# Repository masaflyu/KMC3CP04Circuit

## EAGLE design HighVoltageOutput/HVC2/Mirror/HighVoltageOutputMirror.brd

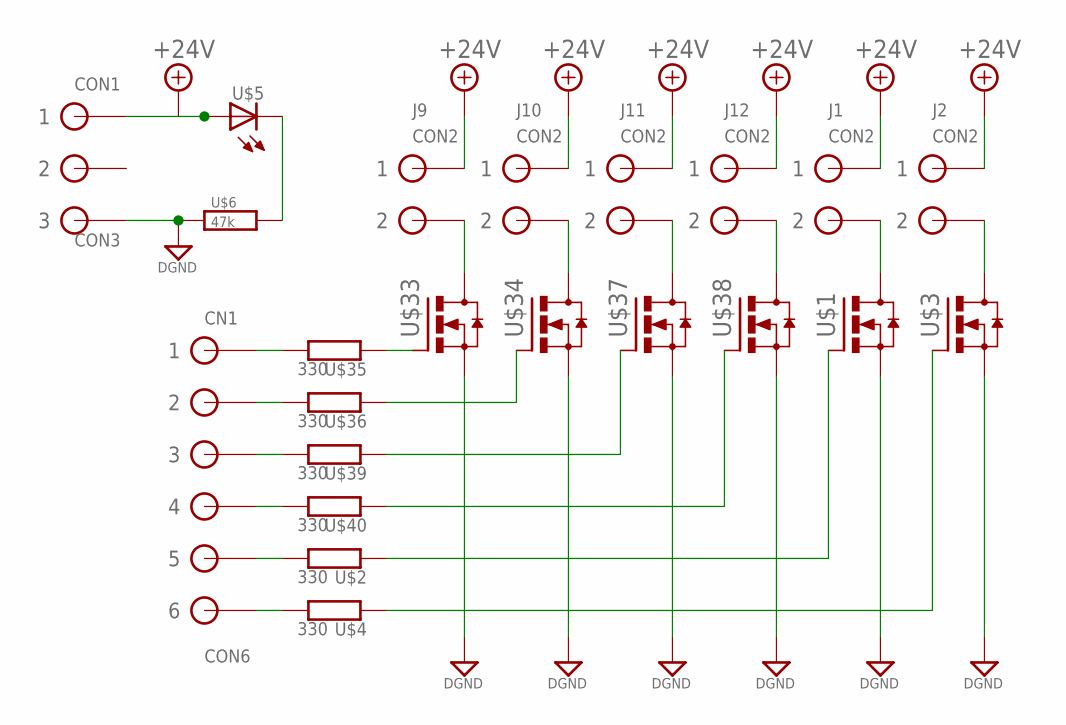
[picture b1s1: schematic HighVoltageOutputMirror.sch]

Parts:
CN1: CON6
CON1: CON3
J1, J2, J9, J10, J11, J12: CON2
U$1, U$3, U$33, U$34, U$37, U$38: TO-252(MOS-FET_N)TO-252FORHAND; TO-252FORHAND
U$2, U$4, U$35, U$36, U$39, U$40: 330; 1/4W-H4_(0207/10)
U$5: LED(砲弾型)3; LED3MM
U$6: 47k; 0805(JIS2012)HAND

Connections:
+24V: CON1.P$1 (1), J1.P$1 (1), J2.P$1 (1), J9.P$1 (1), J10.P$1 (1), J11.P$1 (1), J12.P$1 (1), U$5.A
DGND: CON1.P$3 (3), U$1.2 (S), U$3.2 (S), U$6.1, U$33.2 (S), U$34.2 (S), U$37.2 (S), U$38.2 (S)
unnamed: CN1.P$5 (5), U$2.2
unnamed: U$1.1 (G), U$2.1
unnamed: J1.P$2 (2), U$1.3 (D)
unnamed: CN1.P$6 (6), U$4.2
unnamed: U$3.1 (G), U$4.1
unnamed: J2.P$2 (2), U$3.3 (D)
unnamed: CN1.P$2 (2), U$36.2
unnamed: U$5.K, U$6.2
unnamed: CN1.P$1 (1), U$35.2
unnamed: CN1.P$3 (3), U$39.2
unnamed: CN1.P$4 (4), U$40.2
unnamed: U$33.1 (G), U$35.1
unnamed: U$34.1 (G), U$36.1
unnamed: J9.P$2 (2), U$33.3 (D)
unnamed: J10.P$2 (2), U$34.3 (D)
unnamed: U$37.1 (G), U$39.1
unnamed: U$38.1 (G), U$40.1
unnamed: J11.P$2 (2), U$37.3 (D)
unnamed: J12.P$2 (2), U$38.3 (D)

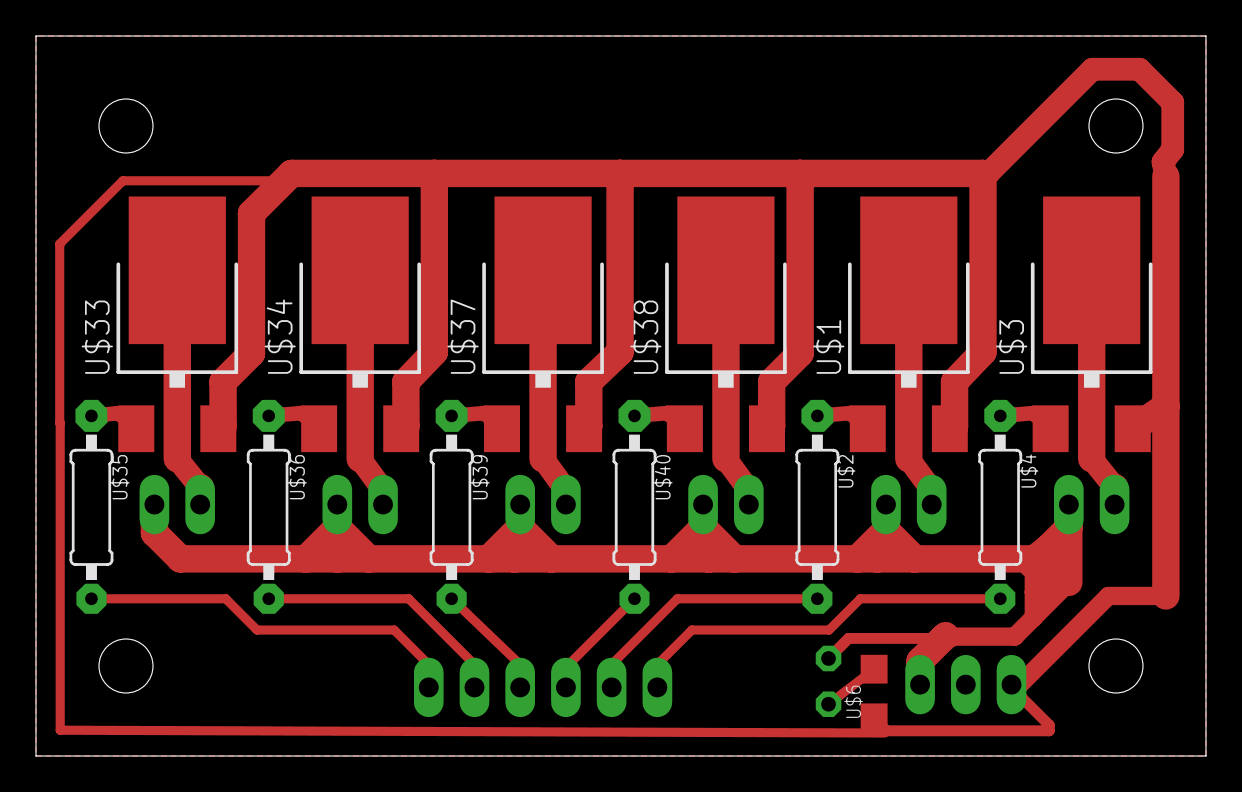
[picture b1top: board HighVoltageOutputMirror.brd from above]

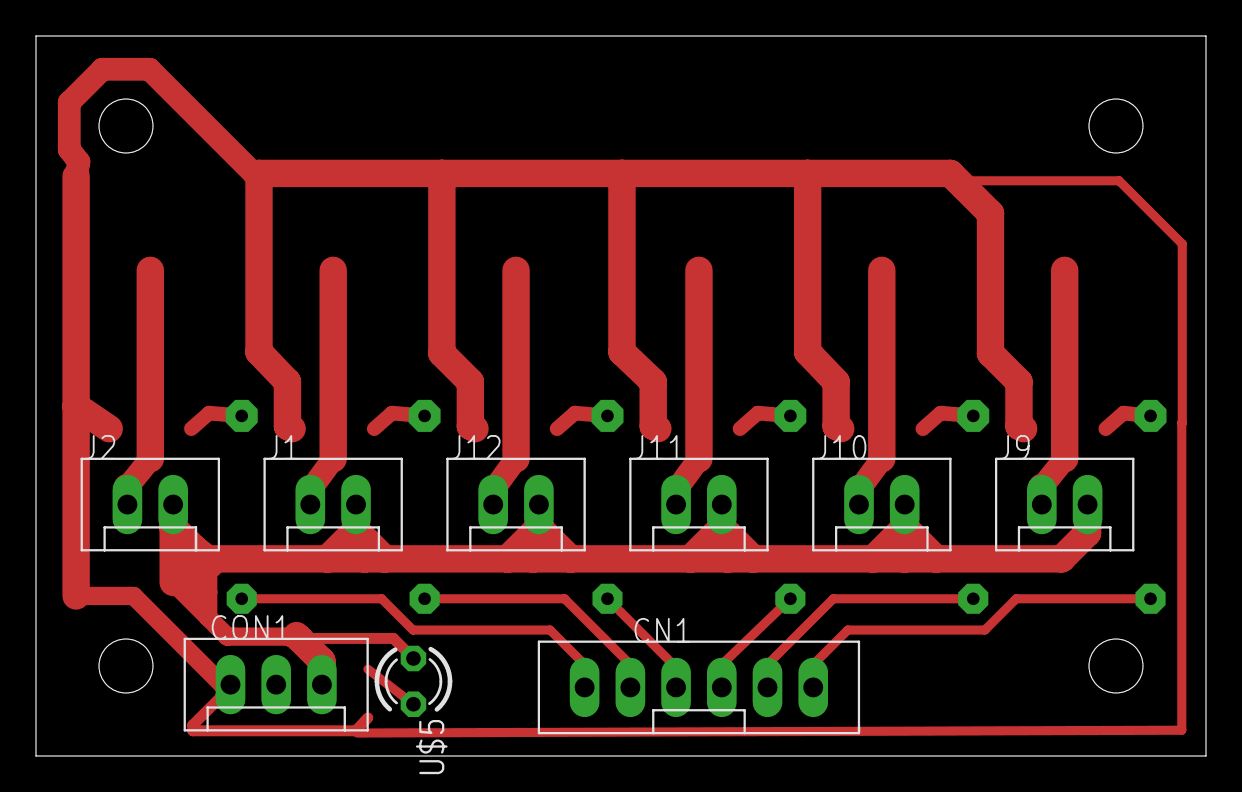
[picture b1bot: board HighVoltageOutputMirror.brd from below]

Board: 2 copper layers, 65.0 x 40.0 mm, 22 parts (9 on the bottom side), 21 nets.

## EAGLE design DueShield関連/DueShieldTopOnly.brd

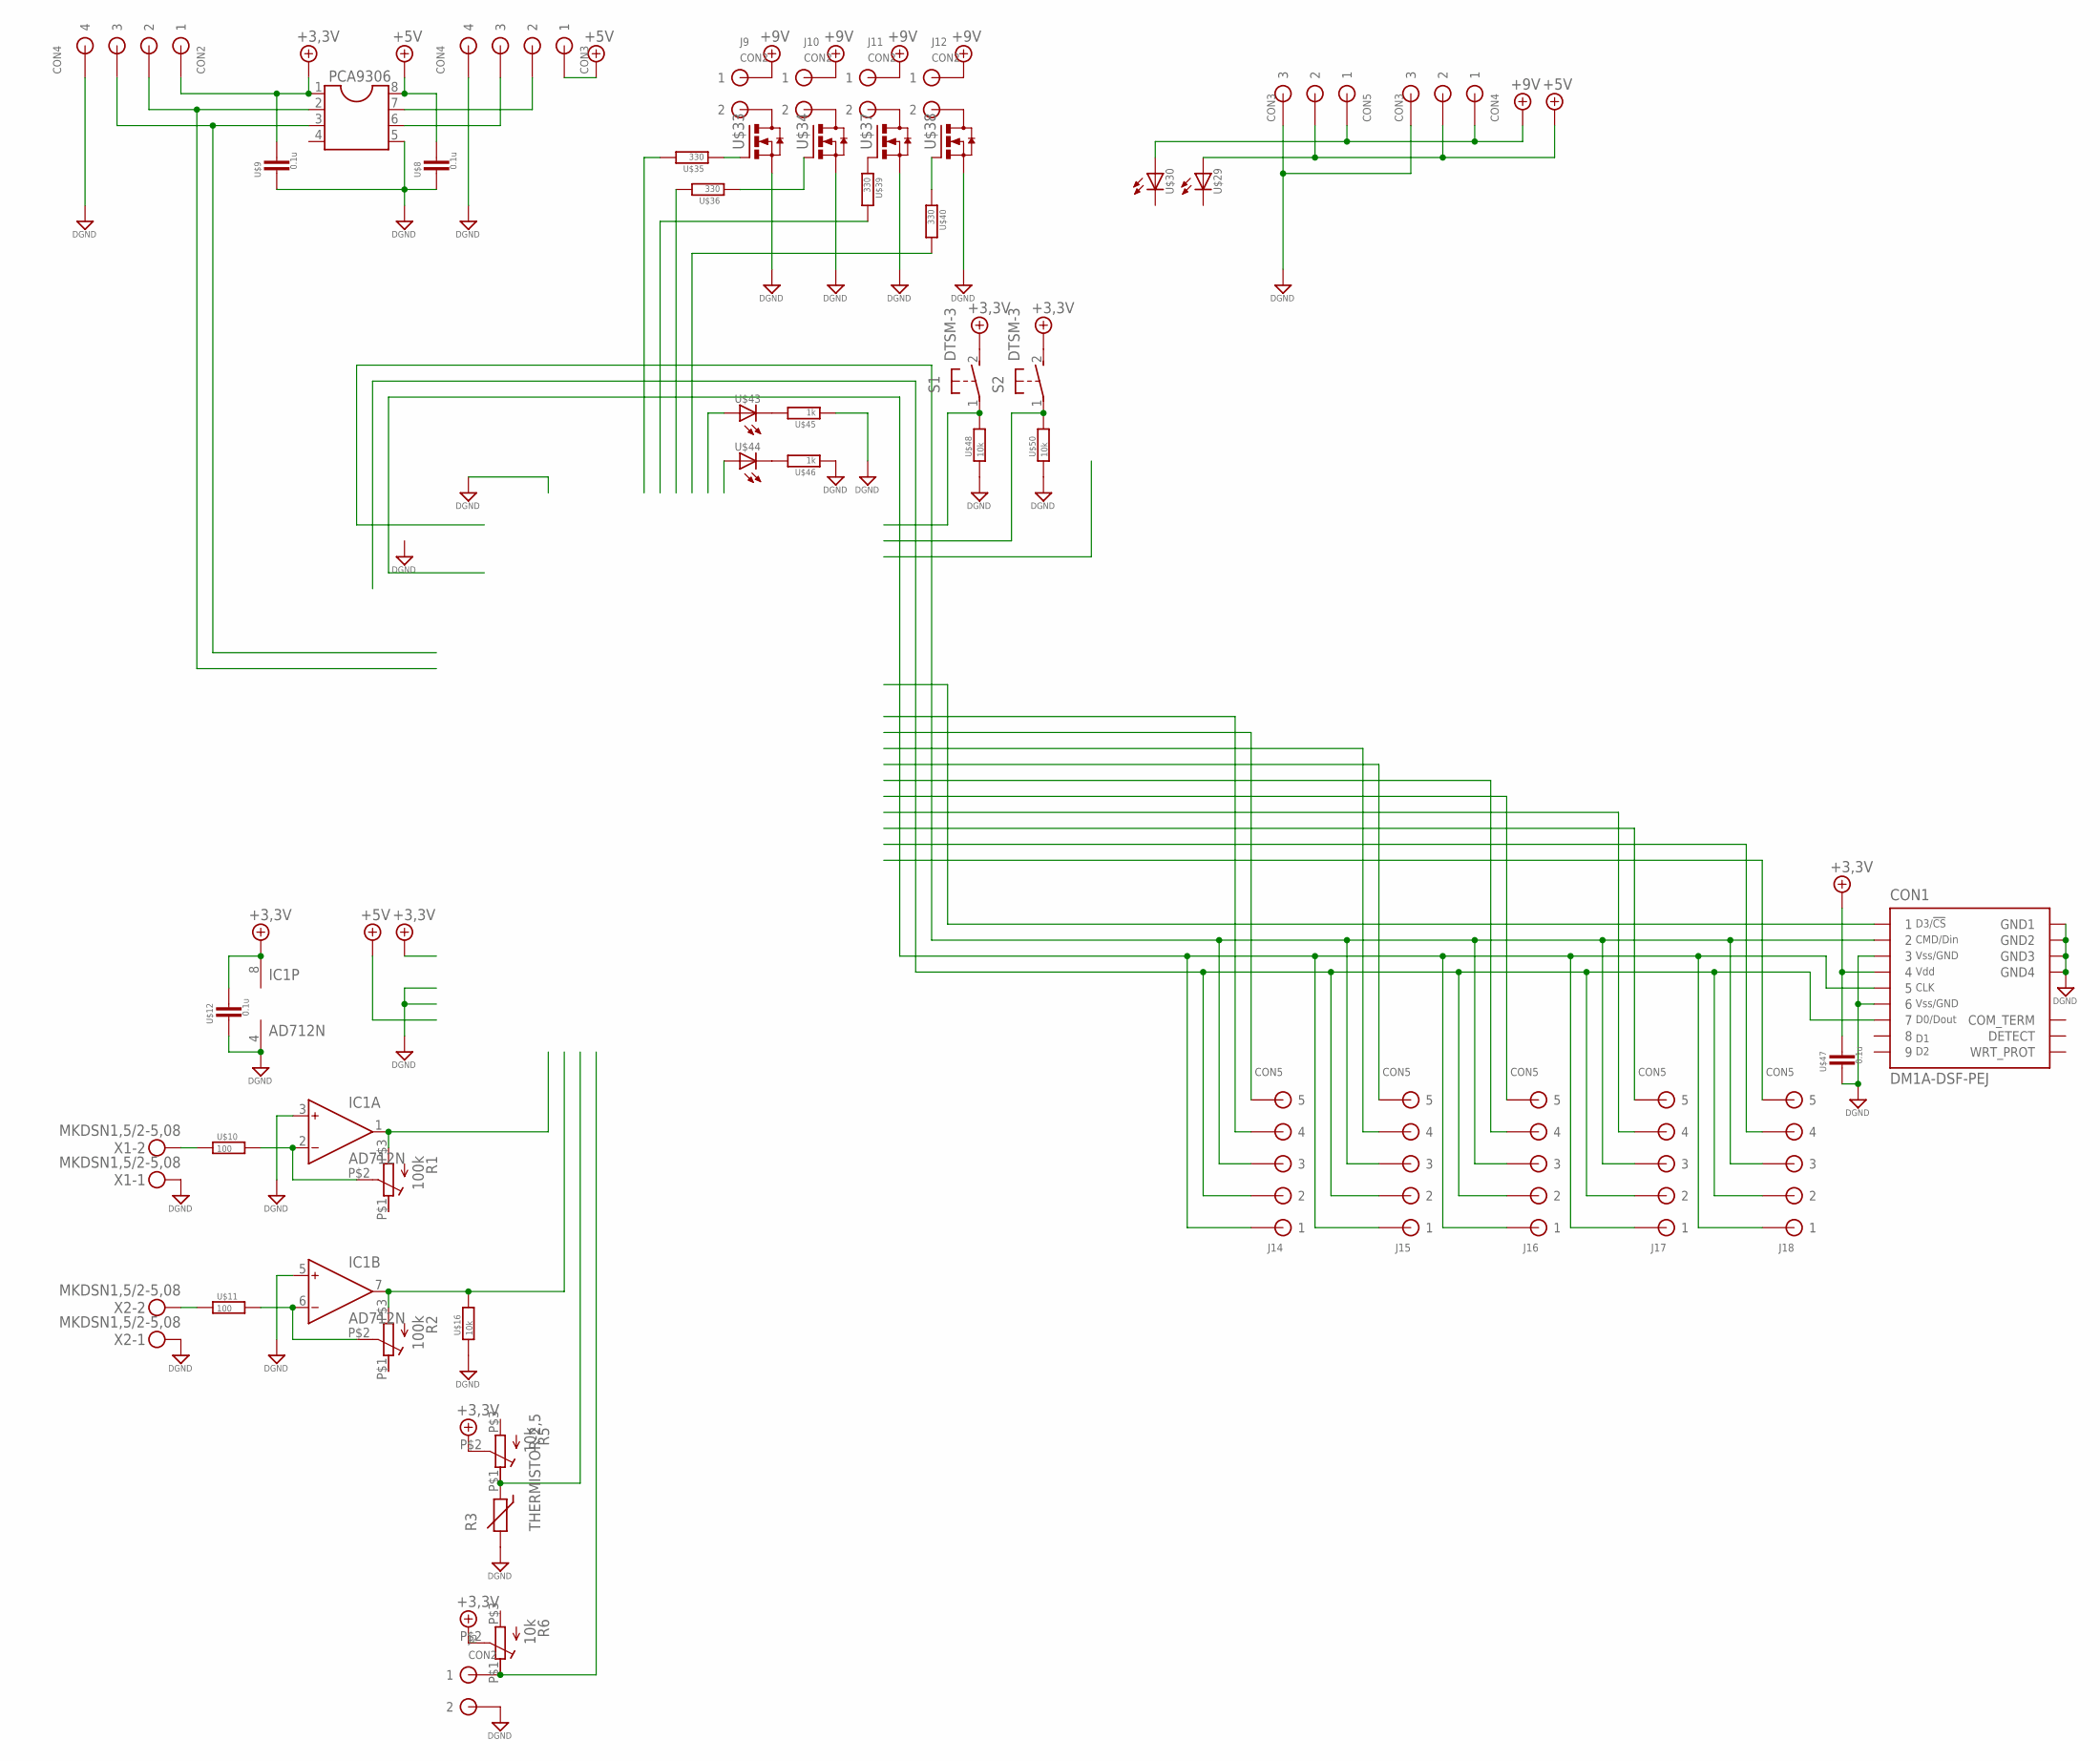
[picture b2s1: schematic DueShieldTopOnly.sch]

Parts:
CON1: DM1A-DSF-PEJ
CON2, CON3: CON4
CON4, CON5: CON3
IC1: AD712N; DIL08
J2, J9, J10, J11, J12: CON2
J14, J15, J16, J17, J18: CON5
PCA9306: DIL8; DIL08
R1, R2: 100k; GF063PB
R3: THERMISTOR-2,5; RS-2,5
R5, R6: 10k; GF063PB
S1, S2: DTSM-3
U$8, U$9, U$12, U$47: 0.1u; 0805
U$10, U$11: 100; 0805
U$16, U$48, U$50: 10k; 0805
U$29, U$30, U$43, U$44: LED(砲弾型)3; LED3MM
U$33, U$34, U$37, U$38: TO-252(MOS-FET_N); TO-252
U$35, U$36, U$39, U$40: 330; 0805
U$45, U$46: 1k; 0805
X1, X2: MKDSN1,5/2-5,08

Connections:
+3.3V: CON1.4, CON2.P$1 (1), IC1.8 (V+), PCA9306.1, R5.P$2 (S), R6.P$2 (S), S1.2, S2.2, U$9.1, U$12.1, U$47.1
+5V: CON3.P$1 (1), CON4.P$2 (2), CON5.P$2 (2), PCA9306.8, U$8.1, U$29.A
+5V1: U$43.A
+9V: CON4.P$1 (1), CON5.P$1 (1), J9.P$1 (1), J10.P$1 (1), J11.P$1 (1), J12.P$1 (1), U$30.A
+9V1: U$44.A
DGND: CON1.3, CON1.6, CON1.GND1, CON1.GND2, CON1.GND3, CON1.GND4, CON2.P$4 (4), CON3.P$4 (4), CON4.P$3 (3), CON5.P$3 (3), IC1.3 (IN+), IC1.4 (V-), IC1.5 (IN+), J2.P$2 (2), PCA9306.5, R3.2, U$8.2, U$9.2, U$12.2, U$16.1, U$33.2 (S), U$34.2 (S), U$37.2 (S), U$38.2 (S), U$45.1, U$46.1, U$47.2, U$48.1, U$50.1, X1.1, X2.1
unnamed: CON1.7, J14.P$2 (2), J15.P$2 (2), J16.P$2 (2), J17.P$2 (2), J18.P$2 (2)
unnamed: S1.1, U$48.2
unnamed: CON2.P$2 (2), PCA9306.2
unnamed: CON1.5, J14.P$1 (1), J15.P$1 (1), J16.P$1 (1), J17.P$1 (1), J18.P$1 (1)
unnamed: CON2.P$3 (3), PCA9306.3
unnamed: CON3.P$2 (2), PCA9306.7
unnamed: CON3.P$3 (3), PCA9306.6
unnamed: IC1.2 (IN-), R1.P$2 (S), U$10.2
unnamed: IC1.6 (IN-), R2.P$2 (S), U$11.2
unnamed: U$11.1, X2.2
unnamed: U$10.1, X1.2
unnamed: J2.P$1 (1), R6.P$1 (E)
unnamed: IC1.1 (OUT), R1.P$3 (A)
unnamed: IC1.7 (OUT), R2.P$3 (A), U$16.2
unnamed: R3.1, R5.P$1 (E)
unnamed: U$43.K, U$45.2
unnamed: U$33.1 (G), U$35.1
unnamed: U$34.1 (G), U$36.1
unnamed: J9.P$2 (2), U$33.3 (D)
unnamed: J10.P$2 (2), U$34.3 (D)
unnamed: U$37.1 (G), U$39.1
unnamed: U$38.1 (G), U$40.1
unnamed: J11.P$2 (2), U$37.3 (D)
unnamed: J12.P$2 (2), U$38.3 (D)
unnamed: U$44.K, U$46.2
unnamed: CON1.2, J14.P$3 (3), J15.P$3 (3), J16.P$3 (3), J17.P$3 (3), J18.P$3 (3)
unnamed: S2.1, U$50.2

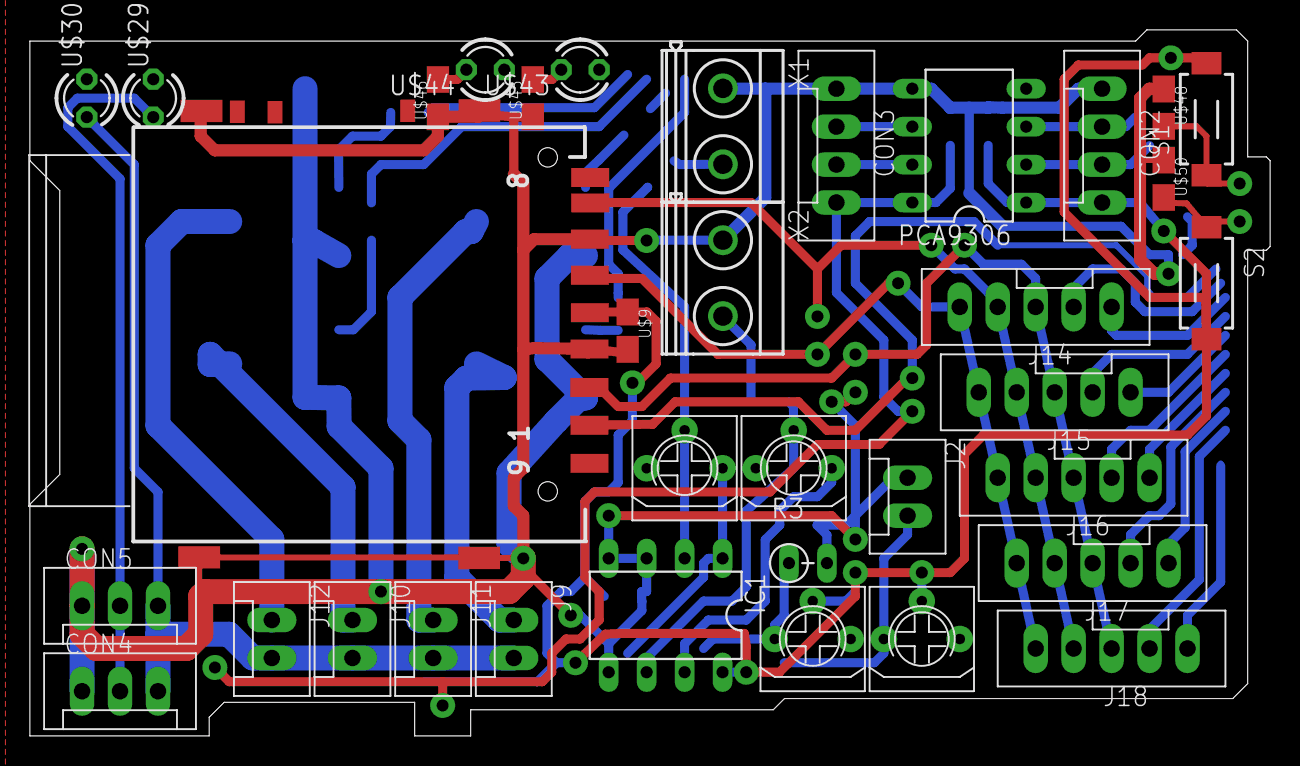
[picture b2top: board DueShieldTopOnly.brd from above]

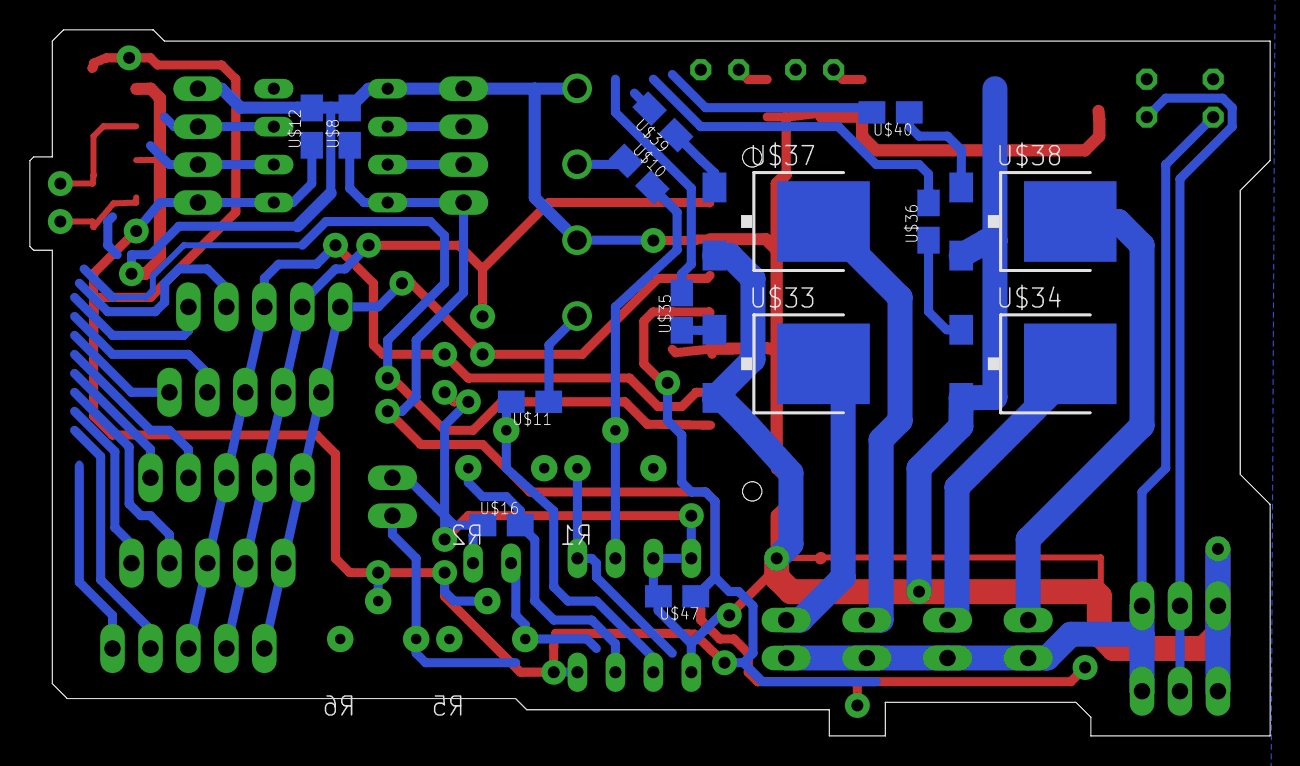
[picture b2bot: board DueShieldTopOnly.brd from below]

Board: 2 copper layers, 83.0 x 47.2 mm, 49 parts (14 on the bottom side), 31 nets.

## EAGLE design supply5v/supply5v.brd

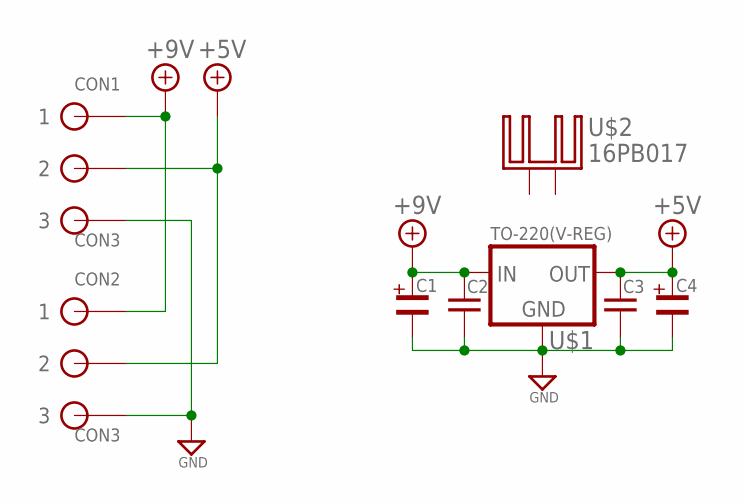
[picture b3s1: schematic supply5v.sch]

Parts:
C1, C4: コンデンサ(電解)E2.5-5; D=1,φ=5
C2, C3: (コンデンサ)セラミック050-024X044; C050-024X044
CON1, CON2: CON3
U$1: TO-220(V-REG); TO-220
U$2: 16PB017

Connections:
+5V: C3.1, C4.+, CON1.P$2 (2), CON2.P$2 (2), U$1.3 (OUT)
+9V: C1.+, C2.1, CON1.P$1 (1), CON2.P$1 (1), U$1.2 (IN)
GND: C1.-, C2.2, C3.2, C4.-, CON1.P$3 (3), CON2.P$3 (3), U$1.1 (GND)

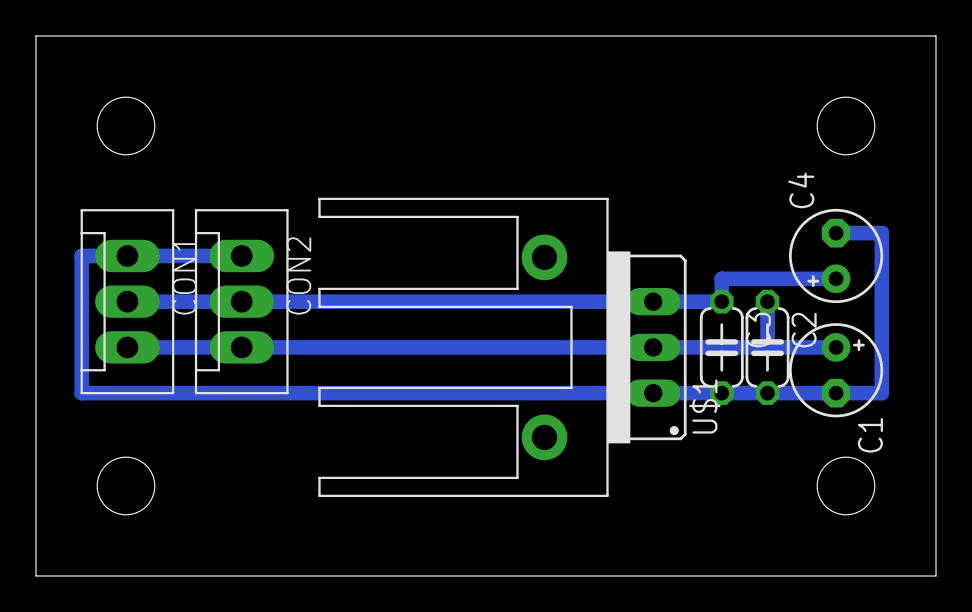
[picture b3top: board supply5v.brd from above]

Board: 2 copper layers, 50.0 x 30.0 mm, 8 parts (0 on the bottom side), 3 nets.

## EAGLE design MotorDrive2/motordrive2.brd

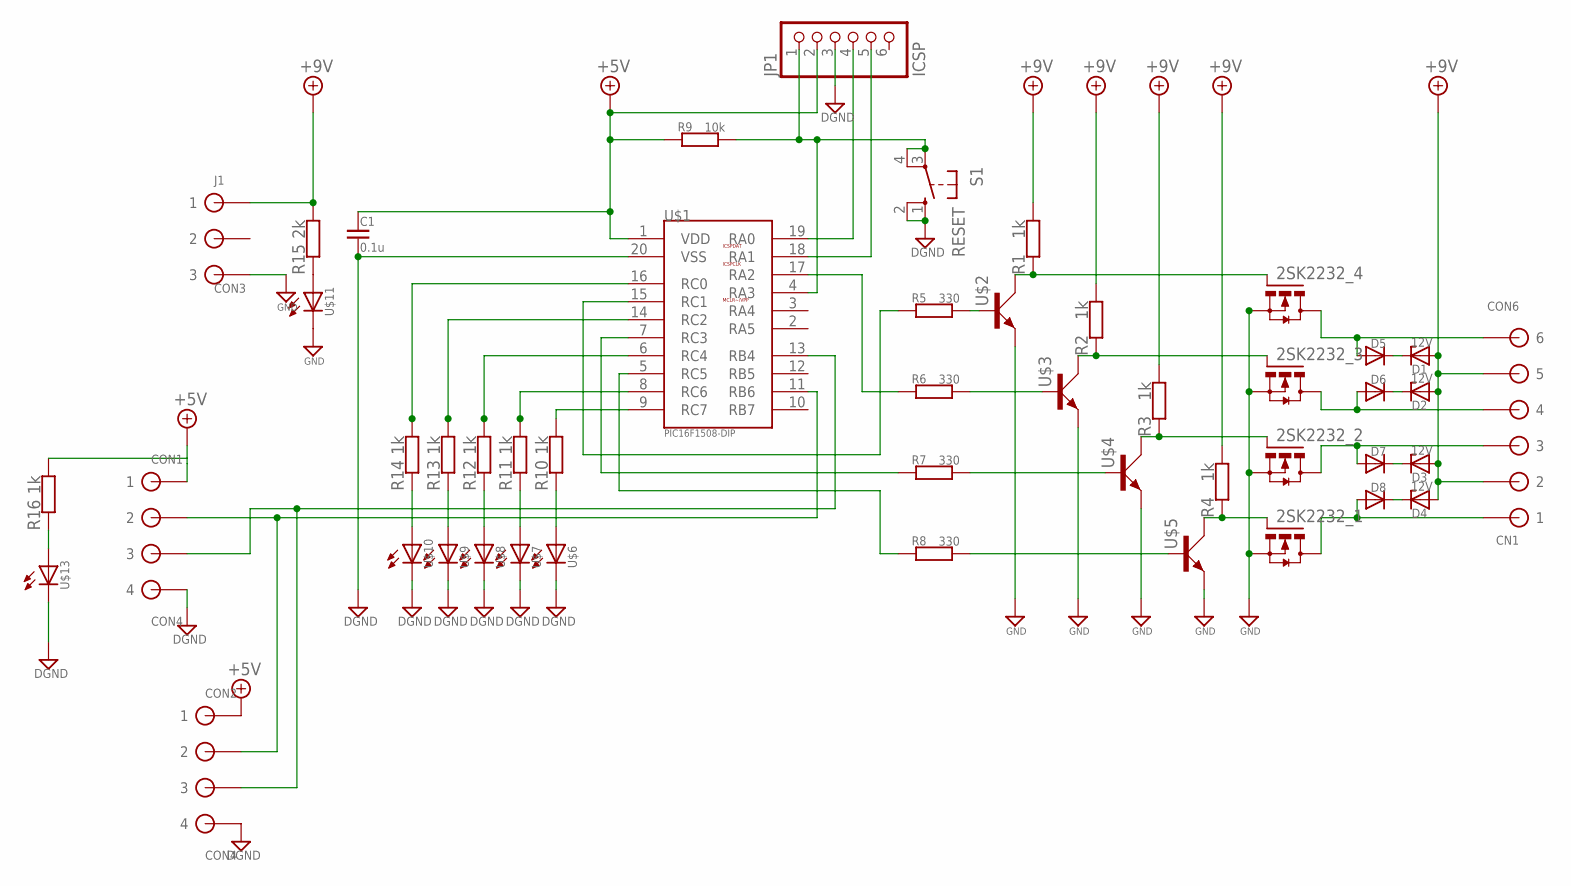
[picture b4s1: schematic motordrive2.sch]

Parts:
2SK2232_1, 2SK2232_2, 2SK2232_3, 2SK2232_4: TO-220(MOS-FET_N); TO-220
C1: 0.1u; C075-032X103
CN1: CON6
CON1, CON2: CON4
D1, D2, D3, D4: 12V; DO41Z(D=3)
D5, D6, D7, D8: (汎用)D=3; DO41(D=3)
J1: CON3
JP1: ICSP; 1X06
R1, R2, R3, R4, R10, R11, R12, R13, R14, R16: 1k; 0207/10
R5, R6, R7, R8: 330; 1/4W-H4_(0207/10)
R9: 10k; 1/4W-H4_(0207/10)
R15: 2k; 0207/10
S1: RESET; B3F-10XX
U$1: PIC16F1508-DIP; DIP254P762X533-20
U$2, U$3, U$4, U$5: TO-92(TRANSISTER_NPN); TO-92
U$6, U$7, U$8, U$9, U$10, U$11, U$13: LED(砲弾型)5; LED5MM

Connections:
+5V: C1.1, CON1.P$1 (1), CON2.P$1 (1), JP1.2, R9.1, R16.2, U$1.1 (VDD)
+9V: CN1.P$2 (2), CN1.P$5 (5), D1.A, D2.A, D3.A, D4.A, J1.P$1 (1), R1.2, R2.2, R3.2, R4.2, R15.2
DGND: C1.2, CON1.P$4 (4), CON2.P$4 (4), JP1.3, S1.1 (S), S1.2 (S1), U$1.20 (VSS), U$6.K, U$7.K, U$8.K, U$9.K, U$10.K, U$13.K
GND: 2SK2232_1.3 (S), 2SK2232_2.3 (S), 2SK2232_3.3 (S), 2SK2232_4.3 (S), J1.P$3 (3), U$2.1 (E), U$3.1 (E), U$4.1 (E), U$5.1 (E), U$11.K
unnamed: 2SK2232_1.2 (D), CN1.P$1 (1), D8.A
unnamed: 2SK2232_2.2 (D), CN1.P$3 (3), D7.A
unnamed: 2SK2232_3.2 (D), CN1.P$4 (4), D6.A
unnamed: 2SK2232_4.2 (D), CN1.P$6 (6), D5.A
unnamed: R8.1, U$1.5 (RC5)
unnamed: R5.1, U$1.15 (RC1)
unnamed: R7.1, U$1.7 (RC3)
unnamed: 2SK2232_3.1 (G), R2.1, U$3.2 (C)
unnamed: CON1.P$2 (2), CON2.P$2 (2), U$1.11 (RB6)
unnamed: R15.1, U$11.A
unnamed: 2SK2232_4.1 (G), R1.1, U$2.2 (C)
unnamed: R6.1, U$1.17 (RA2)
unnamed: 2SK2232_2.1 (G), R3.1, U$4.2 (C)
unnamed: 2SK2232_1.1 (G), R4.1, U$5.2 (C)
unnamed: R5.2, U$2.3 (B)
unnamed: R6.2, U$3.3 (B)
unnamed: R7.2, U$4.3 (B)
unnamed: R8.2, U$5.3 (B)
unnamed: JP1.4, U$1.19 (RA0)
unnamed: JP1.5, U$1.18 (RA1)
unnamed: JP1.1, R9.2, S1.3, S1.4 (P1), U$1.4 (RA3)
unnamed: R16.1, U$13.A
unnamed: R10.1, U$6.A
unnamed: R10.2, U$1.9 (RC7)
unnamed: R11.2, U$1.8 (RC6)
unnamed: R12.2, U$1.6 (RC4)
unnamed: R13.2, U$1.14 (RC2)
unnamed: R14.2, U$1.16 (RC0)
unnamed: R11.1, U$7.A
unnamed: R12.1, U$8.A
unnamed: R13.1, U$9.A
unnamed: D1.C, D5.C
unnamed: D2.C, D6.C
unnamed: D3.C, D7.C
unnamed: D4.C, D8.C
unnamed: R14.1, U$10.A
unnamed: CON1.P$3 (3), CON2.P$3 (3), U$1.13 (RB4)

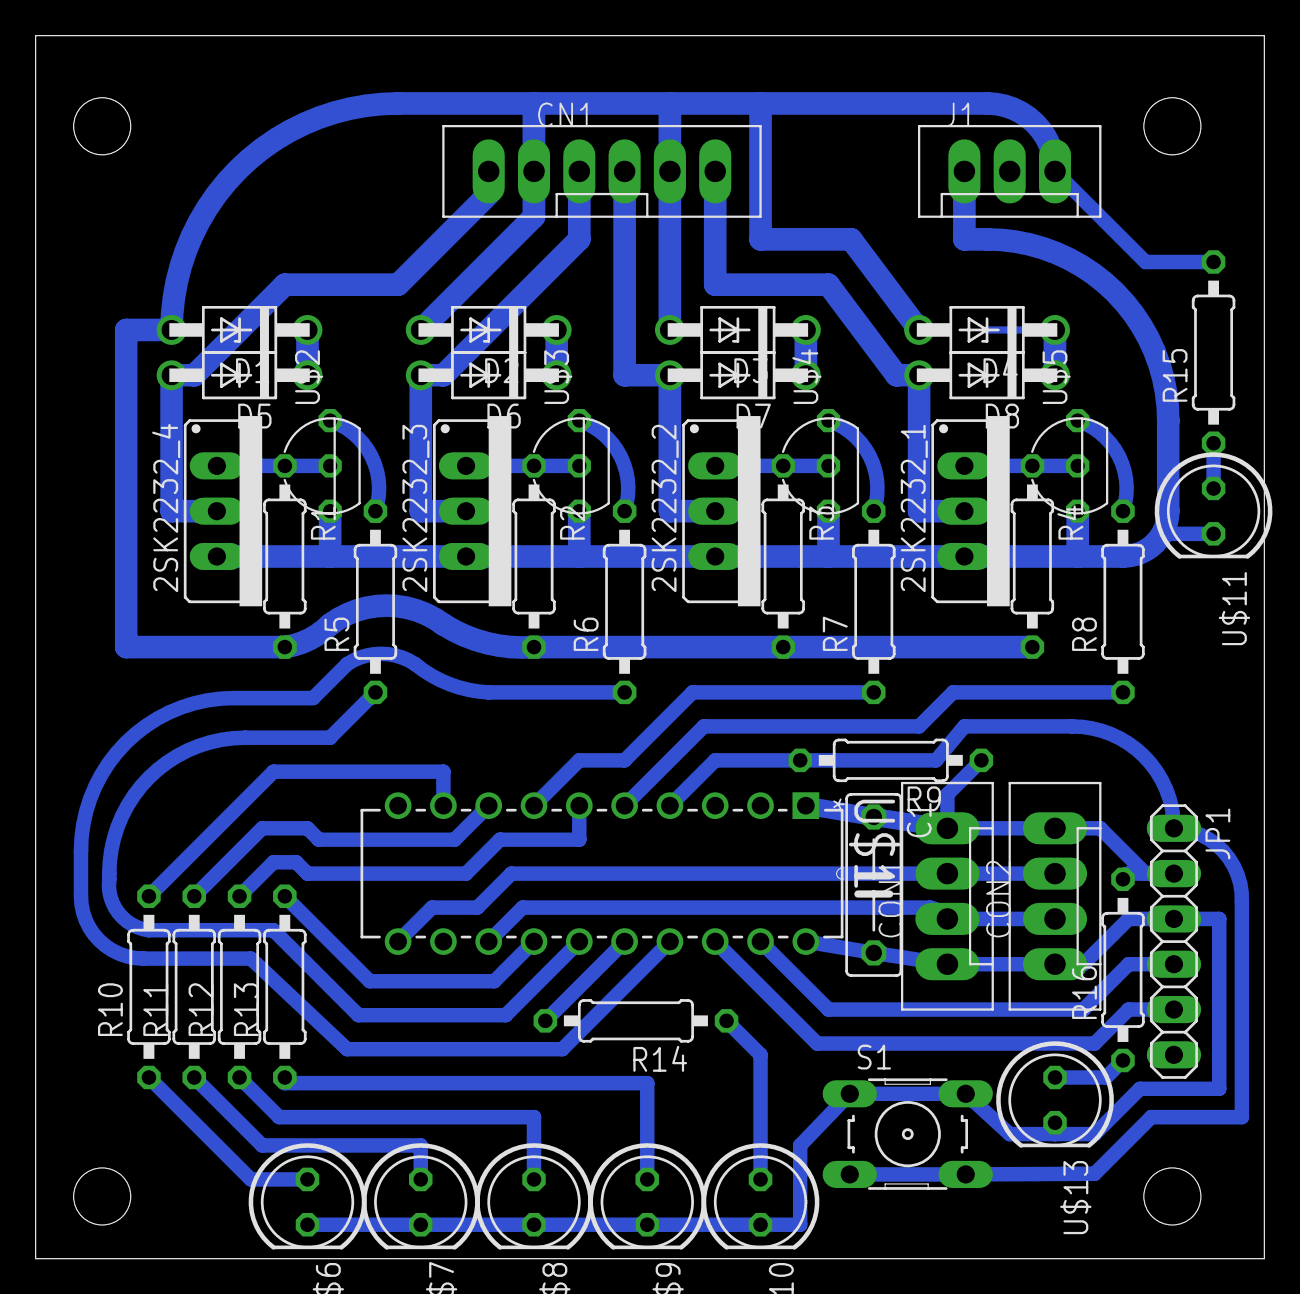
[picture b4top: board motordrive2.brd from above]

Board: 2 copper layers, 68.9 x 68.6 mm, 47 parts (0 on the bottom side), 41 nets.
